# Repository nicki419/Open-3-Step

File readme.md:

# Open 3 Step

Open-Source Circuit and code for custom built 120/240V 3-step (or  n-step) light bulb dimmer working by turning off/on the light switch  quickly to switch between brightness levels. Also provides  memory-functionality to non-memory 3-step bulbs.
Please take the time to read everything. It would mean a lot to me. Otherwise, just move on to docs/howto.md

---

### Background

I want to build a lamp. After making a beautiful frame for it, 3D-designing and printing bulb holders and other components, and buying designer LED bulbs (3 pairs of different bulbs, for a total of 6), I discovered that four of those bulbs were 3-step dimmable, and two were TRIAC dimmable. I therefore set out to make my TRIAC bulbs 3-step dimmable, with a memory function, so they could work with my 3-step bulbs.

I soldered a 5V power supply with some fuses, capacitors and resistors to a 30x70mm prototyping board, did the same for an ATMEGA328P, an EEPROM and some GPIO headers, wrote the arduino sketch (see v0.1 code) and it worked, after lots of debugging. If not for the next thing I discovered, this repository would not exist.

The dimming worked. The memory worked. Then it hit me. All four of my 3-step dimmable bulbs are from the same company, and have the exact same box design, with a myriad of icons on the side showing its features. Only after making v0.1 did I realise that two of the bulbs did NOT have a memory function, and two more did. So I now had four bulbs with memory, and two without. Since I also bought regular AC switch modules next to the RBDimmer module, I decided to make another version that would also control the two 3-step bulbs without memory.

Over the summer, I learned the basics of PCB Design and ordered my boards for the next version. I got some more components to make this project more easily customisable and added potentiometers for more easy brightness control at the three steps, as well as support for the non-memory 3-step bulbs.

### Versions

**0.2**

This version will implement the features described above on a custom PCB. All the components will, however, also fit on a 30x70mm prototyping board, if you really want to go that route.

To not clutter the repo, I will share exported PDFs, gerber files, STLs, etc. only via releases.

Changelog:

- Add Support for non-memory 3-step bulbs through fast switching when the system powers up
- Add analogue input via 100K potentiometers and a button to configure the brightness levels outside of code
- Move from arduino to platformio and add separate debug and release profiles (release will have no LED blinking)
- Create Settings Mode for configuring brightnesses and saving into EEPROM
- Create 3-step calibration mode to find out how long the delay in your bulbs is.

**0.1**

The original version is fully implementable on prototyping boards. This is also where the power supply comes from. I chose not to create schematics for the power supply, but there is documentation on what's required and recommended when creating it. If you only need 3-step dimming with a memory function, you may use the code from both v0.1 and v0.2. They should hopefully be cross-compatible, as the new board only adds things, it doesn't modify any existing pins. Consult the documentation of the v0.2 code once it fully releases on how to do this. During development, you probably want to use the v0.1 code, instead.

Therefore, you can refer to the schematics for v0.2 on how to wire everything. You simply need to leave out the push button, potentiometers, and the additional GPIO pin for the AC switch. You also need to configure the values for your bulb in code. For v0.2, I will place these in a header file, for v0.1, there is an array defined at the top of the code.

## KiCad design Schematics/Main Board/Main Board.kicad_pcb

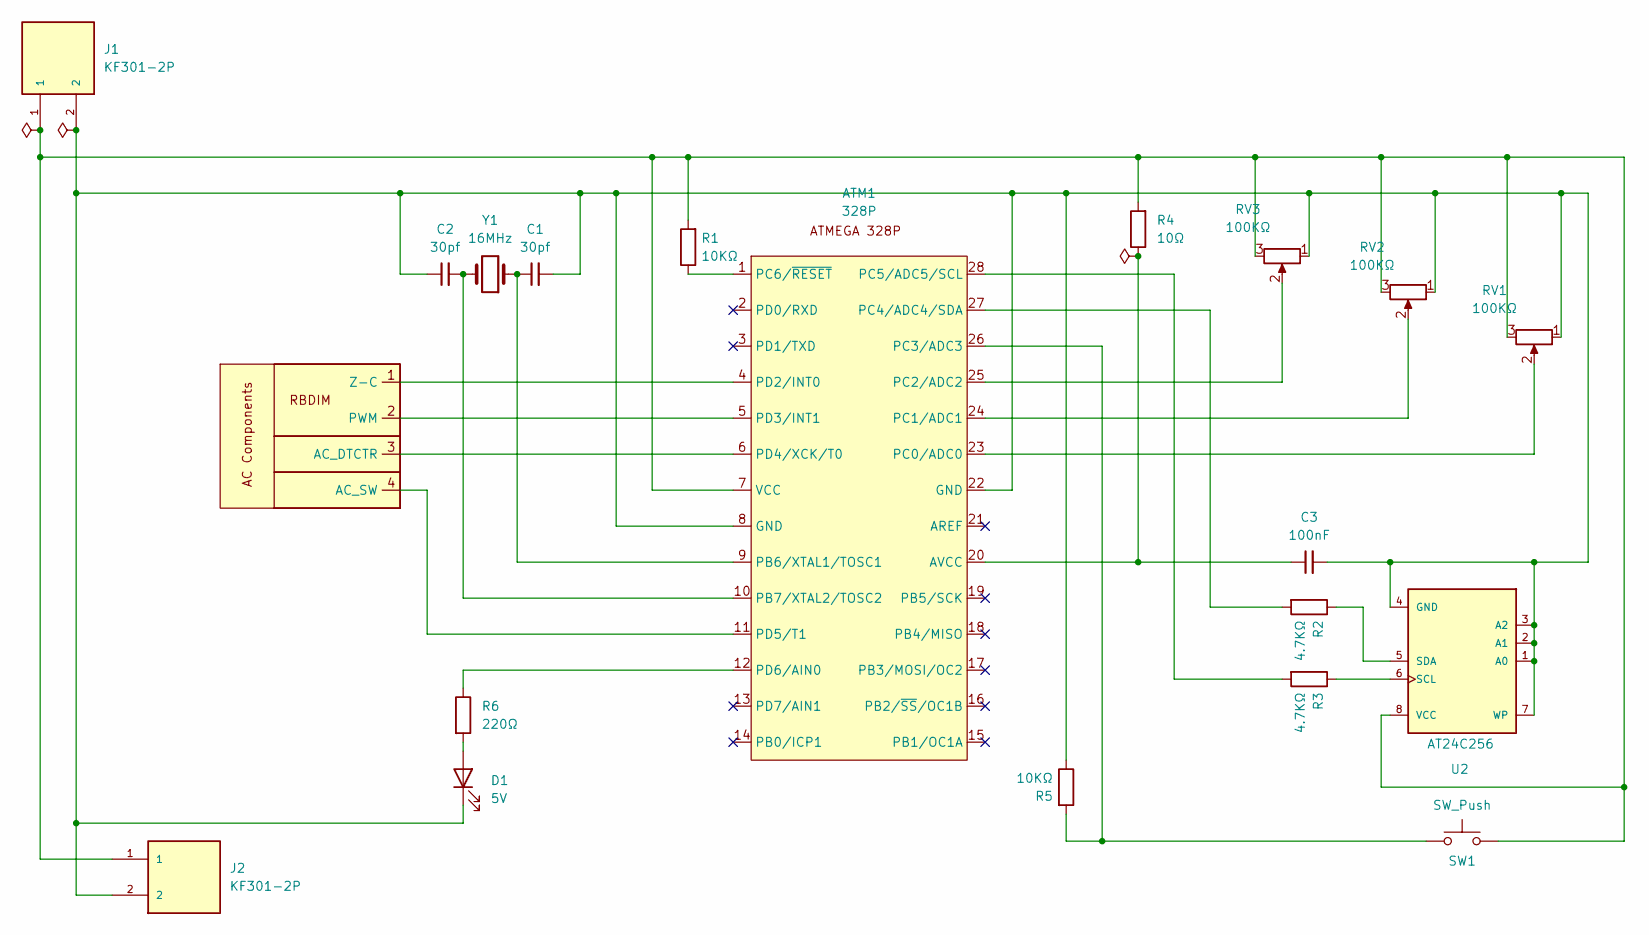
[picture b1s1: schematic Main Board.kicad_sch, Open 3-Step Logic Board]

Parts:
ATM1: 328P; DIP794W46P254L2967H457Q28B
C1, C2: 30pf; C_Disc_D3.0mm_W1.6mm_P2.50mm
C3: 100nF; C_Disc_D3.0mm_W1.6mm_P2.50mm
D1: 5V; LED_D5.0mm
J1, J2: KF301-2P; HANDSON_KF301-2P; PARTREV NA
R1, R5: 10KΩ; R_Axial_DIN0207_L6.3mm_D2.5mm_P7.62mm_Horizontal
R2, R3: 4.7KΩ; R_Axial_DIN0207_L6.3mm_D2.5mm_P7.62mm_Horizontal
R4: 10Ω; R_Axial_DIN0207_L6.3mm_D2.5mm_P7.62mm_Horizontal
R6: 220Ω; R_Axial_DIN0207_L6.3mm_D2.5mm_P7.62mm_Horizontal
RV1, RV2, RV3: 100KΩ; Potentiometer_Runtron_RM-065_Vertical
SW1: SW_Push; SW_PUSH_6mm_H5mm
U1: PinHeader_1x04_P2.54mm_Vertical
U2: AT24C256; DIP787W46P254L927H533Q8
Y1: 16MHz; Crystal_HC49-U_Vertical

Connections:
unnamed: ATM1.20 (AVCC), C3.1, R4.1
unnamed: ATM1.9 (PB6/XTAL1/TOSC1), C1.1, Y1.1
unnamed: ATM1.10 (PB7/XTAL2/TOSC2), C2.2, Y1.2
unnamed: ATM1.23 (PC0/ADC0), RV1.2
unnamed: ATM1.24 (PC1/ADC1), RV2.2
unnamed: ATM1.25 (PC2/ADC2), RV3.2
unnamed: ATM1.26 (PC3/ADC3), R5.2, SW1.1
unnamed: ATM1.27 (PC4/ADC4/SDA), R2.2
unnamed: ATM1.28 (PC5/ADC5/SCL), R3.2
unnamed: ATM1.1 (PC6/~RESET), R1.1
unnamed: ATM1.4 (PD2/INT0), U1.1 (Z-C)
unnamed: ATM1.5 (PD3/INT1), U1.2 (PWM)
unnamed: ATM1.6 (PD4/XCK/T0), U1.3 (AC_DTCTR)
unnamed: ATM1.11 (PD5/T1), U1.4 (AC_SW)
unnamed: ATM1.12 (PD6/AIN0), R6.1
unnamed: ATM1.7 (VCC), J1.1, J2.1, R1.2, R4.2, RV1.3, RV2.3, RV3.3, SW1.2, U2.8 (VCC)
unnamed: D1.2 (A), R6.2
unnamed: ATM1.8 (GND), ATM1.22 (GND), C1.2, C2.1, C3.2, D1.1 (K), J1.2, J2.2, R5.1, RV1.1, RV2.1, RV3.1, U2.1 (A0), U2.2 (A1), U2.3 (A2), U2.4 (GND), U2.7 (WP)
unnamed: R3.1, U2.6 (SCL)
unnamed: R2.1, U2.5 (SDA)

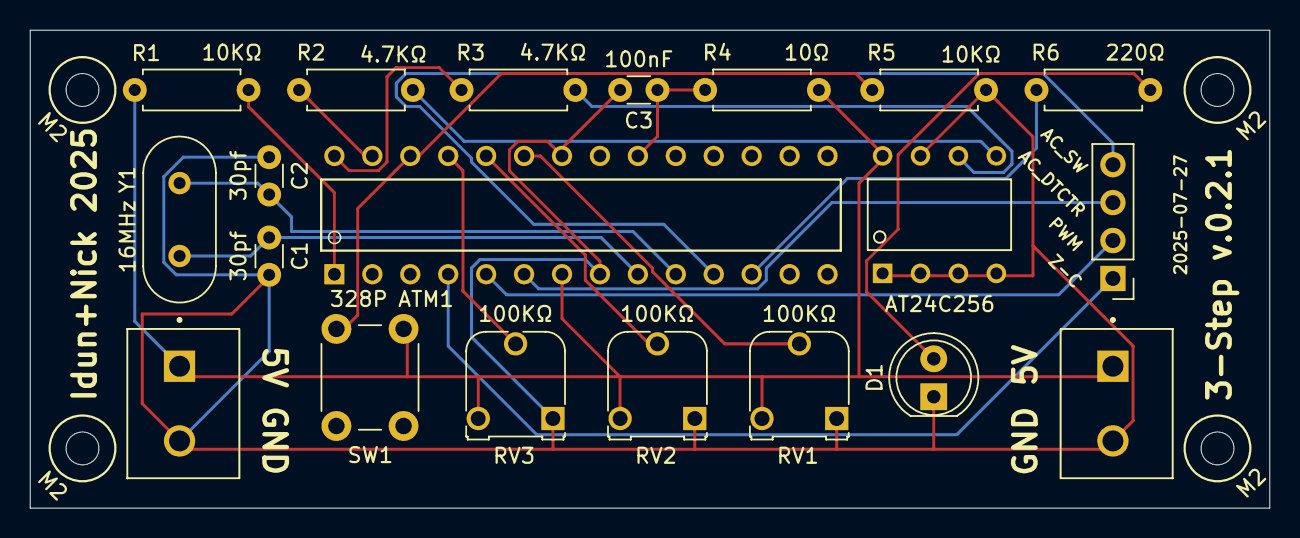
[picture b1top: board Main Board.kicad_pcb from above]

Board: 2 copper layers, 83.0 x 32.0 mm, 20 parts (0 on the bottom side), 20 nets.

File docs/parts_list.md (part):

# Parts List

This file covers the parts required for both v0.1, v0.2, and the power supply.

An asterisk denotes parts optional, but recommended. Links are non-affiliate AliExpress Links. I cannot guarantee that these will remain online, and I will not actively update them.

### General Purpose
These are "universal" parts you will need either way, so I will list them here. I will not add links because they are easy enough to find
- Solid Core Wire (both for soldering and connecting between terminal connectors
- GPIO Jumper Cables. Recommend you get Male to Male, Male to Female, and Female to Female. 
- Solder (duh)
- Flux/Rosin
- "Wire solder holder" (for lack of better description) Highly recommended because you'll likely solder gpio cables to thicker ones
  https://www.aliexpress.com/item/1005009535618361.html
- Stranded Wire rated for 240V 
- M2 and M3 Brass Screw inserts (M3 only needed for the RBDimmer. You can use M2 as well and use 3D-printed washers)

### V0.2 PCB
You have many options of ordering your PCB. I went with PCBWay because they offer IOSS (EU Vat prepaid) shipping methods, which is essential for delivery to where I live. Should you also choose PCBWay and have not ordered with them before, I would appreciate if you signed up using my referral link. You will get \$5 off on your first order, I get \$10 in coupons. That's all there's to it. [Click here <3](https://pcbway.com/g/Qr5ZNd)

### Power Supply

![Power Supply Unit](img/psu.jpg)

| Qty                | Part                               | Link                                                  |
|--------------------|------------------------------------|-------------------------------------------------------|
| 1                  | 30x70mm Prototyping Board          | https://www.aliexpress.com/item/1005009550650037.html |
| 1                  | HLK-PM01 Power Supply Unit         | https://www.aliexpress.com/item/1005007038304937.html |
| 2 (3*)<sup>1</sup> | KF301 2 Pin Terminal Connector     | https://www.aliexpress.com/item/1005006642865467.html |
| 2                  | 4700µF 10V Electrolytic Capacitors | https://www.aliexpress.com/item/1005008896677668.html |
| 1*                 | 5x20mm 250V 0.5A Slow-Blow Fuse    | https://www.aliexpress.com/item/32871909497.html      |
| 1*                 | 5x20mm Fuse Holder                 | https://www.aliexpress.com/item/1005005645173789.html |
| 1*<sup>1</sup>     | 73° Thermal Fuse                   | https://www.aliexpress.com/item/1940867762.html       |
| 1                  | 10Ω Resistor                       | https://www.aliexpress.com/item/1005009329218922.html |

**Notes**

1. A third terminal connector I have used to mount the Thermal fuse. This is not good practice and you should probably use a connector made for these fuses.
   Do not make the same mistake as I and try to solder them. Turns out thermal fuses blow when they get hot. ;)

**Instructions**

- Fuses are in Series with the live line of your input. Their order should not matter, as the thermal fuse can handle 10A.
- Capacitors are in parallel with the HLK-PM01 output lines.
- The Resistor is in Series with the HLK-PM01's VCC output line after the caps.
- Use silicon rubber thermal glue to attach the thermal fuse to the HLK-PM01.


### v0.1
![V0.1 Board](img/v0.1_board.jpg)

| Qty                | Part                             | Link                                                  |
|--------------------|----------------------------------|-------------------------------------------------------|
| 1                  | 30x70mm Prototyping Board        | https://www.aliexpress.com/item/1005009550650037.html |
| 1 (2*)<sup>1</sup> | KF301 2 Pin Terminal Connector   | https://www.aliexpress.com/item/1005006642865467.html |
| 1<sup>2</sup>      | 16 MHz HC-49S Crystal Oscillator | https://www.aliexpress.com/item/1005005293770220.html |
| 2<sup>2</sup>      | 30pF Ceramic Capacitor           | https://www.aliexpress.com/item/1005007792464333.html |
| 1                  | 5V LED                           | https://www.aliexpress.com/item/1005009402134026.html |
| 1                  | 10KΩ Resistor                    | https://www.aliexpress.com/item/1005009329218922.html |
| 1                  | 220Ω Resistor                    | https://www.aliexpress.com/item/1005009329218922.html |
| 2<sup>3</sup>      | 4.7KΩ Resistor                   | https://www.aliexpress.com/item/1005009329218922.html |
| 1                  | 28 Pin Narrow DIP Socket         | https://www.aliexpress.com/item/1005006256010892.html |
| 1                  | 8 Pin Narrow DIP Socket          | https://www.aliexpress.com/item/1005006256010892.html |
| 1                  | ATMEGA328P DIP                   | https://www.aliexpress.com/item/1005008144708950.html |
| 1                  | AT24C256 DIP                     | https://www.aliexpress.com/item/1005006779000585.html |
| 1<sup>4</sup>      | 1x3 pin Male GPIO Headers        | https://www.aliexpress.com/item/1005003323489438.html |

**Notes**
1. You only need one for input. But I recommend one at the other side of the board for output to the components that have their own PCB.
2. I recommend you find a listing that specifies the load capacitance, like the one I linked. You can then calculate the exact capacitor values needed for your load capacitors.
   Formula: C = 2 × (CL - Cstray) where CL is the load capacitance, and Cstray is the stray capacitance (typically 5pF)
3. My original v0.1 board did not have these, and it worked, but that turned out to be dumb luck. I highly recommend you add them.
   Needed for I2C communication between the ATMEGA328P and the AT24C256.
4. Buy any size, unlike the female ones, these are easy to cut.


### v0.2

![V0.2 PCB](img/v0.2_pcb.png)

| Qty           | Part                             | Link                                                   |
|---------------|----------------------------------|--------------------------------------------------------|
| 1             | PCB from Repo                    | [My PCBWay Referral Link](https://pcbway.com/g/Qr5ZNd) |
| 2             | KF301 2 Pin Terminal Connector   | https://www.aliexpress.com/item/1005006642865467.html  |
| 1<sup>1</sup> | 16 MHz HC-49S Crystal Oscillator | https://www.aliexpress.com/item/1005005293770220.html  |
| 2<sup>1</sup> | 30pF Ceramic Capacitor           | https://www.aliexpress.com/item/1005007792464333.html  |
| 1             | 100nF Ceramic Capacitor          | https://www.aliexpress.com/item/1005007792464333.html  |
| 1             | 5V LED                           | https://www.aliexpress.com/item/1005009402134026.html  |
| 2             | 10KΩ Resistor                    | https://www.aliexpress.com/item/1005009329218922.html  |
| 1             | 220Ω Resistor                    | https://www.aliexpress.com/item/1005009329218922.html  |
| 2             | 4.7KΩ Resistor                   | https://www.aliexpress.com/item/1005009329218922.html  |
| 1             | 10Ω Resistor                     | https://www.aliexpress.com/item/1005009329218922.html  |
| 1             | 28 Pin Narrow DIP Socket         | https://www.aliexpress.com/item/1005006256010892.html  |
| 1             | 8 Pin Narrow DIP Socket          | https://www.aliexpress.com/item/1005006256010892.html  |
| 1             | ATMEGA328P DIP                   | https://www.aliexpress.com/item/1005008144708950.html  |
| 1             | AT24C256 DIP                     | https://www.aliexpress.com/item/1005006779000585.html  |
| 1<sup>2</sup> | 1x4 pin Male GPIO Headers        | https://www.aliexpress.com/item/1005003323489438.html  |
| 1             | 6x6mm TS-D001 Tactile Switch     | https://www.aliexpress.com/item/1005004159746274.html  |
| 3             | RM065 100KΩ Potentiometers       | https://www.aliexpress.com/item/1005003523757457.html  |

**Notes**
1. See v0.1 Note 2
2. See v0.1 Note 4


### Other
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
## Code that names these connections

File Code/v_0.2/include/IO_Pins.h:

//
// Created by nick on 05/08/25.
//

#ifndef IO_PINS_H
#define IO_PINS_H

#define MAINS_DETECT_PIN PD4     // Mains detector output (LOW = mains present)
#define ZERO_CROSS_PIN PD2       // Zero-cross input for dimmer timing
#define DIMMER_PIN PD3           // Dimmer PSM output
#define STATUS_LED_PIN PD6       // External status LED
#define AC_SW_PIN PD5            // AC switch output

#define POT1_PIN A0             // ADC2 (PC2/A2)
#define POT2_PIN A1             // ADC1 (PC1/A1)
#define POT3_PIN A2             // ADC0 (PC0/A0)
#define BUTTON_PIN A3           // ADC3 (PC3/A3) Used as digital input

#endif //IO_PINS_H

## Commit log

2025-08-05 Initial Commit - v0.1 Code - v0.2 Empty PIO Project - Kicad Project for the main logic circuit - OpenSCAD Files for (P)CB mounts
2025-08-05 Remove Gerber Files; Update gitignore
2025-08-05 Refactor v0.1 code towards OOP and PIO
2025-08-05 Add Debug and Release Environments
2025-08-05 Implement CLion Refactoring Suggestions
2025-08-05 Move git submodule location to lib
2025-08-05 v0.2-code (#1)
    * Refactor v0.1 code towards OOP and PIO
    * Add Debug and Release Environments
2025-08-05 fix gitmodules
2025-08-05 Added readme.md and parts_list.md
2025-08-05 Added mounts.md
2025-08-05 documentation (#3)
    * Added readme, parts list, and 3d-print mounts documentation
    * fix gitmodules
2025-08-05 Added M2 version of the AC Dimmer Mount
2025-08-06 Implement SettingsController and EdgeDetector
2025-08-06 Read brightness from eeprom when cycling
2025-08-10 Fixed write to eeprom failing and current brightness index mismatch between brightness controller and main
2025-08-10 Removed edge detector in favour of OneButtonTiny library -> fixed bug of entering settings mode
2025-08-10 Fixed reading brightness from eeprom issues and finished settings mode
2025-08-10 Changed Delay to 500ms in a definition
2025-08-31 Updated AC Switch mount to new component, added washers to each component separately
2025-08-31 Added extra config to platformio.ini
2025-08-31 Implement SettingsController and EdgeDetector (#5)
    * Implement SettingsController
    * Read brightness from eeprom when cycling
    * Changed Delay to 500ms in a definition
    * Added extra config to platformio.ini
2025-08-31 Fixed length of AC Switch Mount
2025-08-31 Updated image and docs for new relay
2025-08-31 Updated AC Switch mount to new component, added washers to each compo… (#6)
    * Updated AC Switch mount to new component, added washers to each component separately
    * Updated image and docs for new relay
2025-08-31 Dimming of non-memory 3-step lamps
2025-08-31 Implement test mode for 3-step dimmable bulbs w/o memory
2025-08-31 Ac dimmer implementation (#7)
    * Dimming of non-memory 3-step lamps
    * Implement test mode for 3-step dimmable bulbs w/o memory
2025-09-01 Added Release script and github workflow for auto release
2025-09-01 Finished Documentation (I think)
2025-09-01 Documentation 2 (#8)
    * Added Release script and github workflow for auto release
    * Finished Documentation (I think)
2025-09-01 Fix release workflow
2025-09-01 Revert "Fix release workflow"
    This reverts commit 3ebdfbe8306a55c39780f5136e40eeff3c86557e.
2025-09-01 Fix workflow (#9)
    * Fix release workflow
2025-09-01 Fix release workflow attempt 2
2025-09-01 Fix workflow (#10)
    * Fix release workflow attempt 2
2025-09-01 Fix release workflow attempt 3
2025-09-01 Fix workflow (#11)
    * Fix release workflow attempt 3
2025-09-01 I give up. Doing releases manually.
2025-09-01 Fix workflow (#12)
    * delete workflow
2025-09-01 Fix resistor placement in parts list instructions
2025-09-01 Fix resistor placement in parts list instructions (#13)
